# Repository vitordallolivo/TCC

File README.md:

<div align="center">

# DESENVOLVIMENTO DE SISTEMA DE AQUISIÇÃO COM ESTIMAÇÃO POR MODO DESLIZANTE PARA BANCADA DE PROPULSÃO COM MOTOR BLDC

**Trabalho de Conclusão de Curso · Engenharia Elétrica · UDESC Joinville (2026)**

-283272)

</div>

---

## Sumário

- [Sobre o projeto](#sobre-o-projeto)
- [Arquitetura](#arquitetura)
- [Estrutura do repositório](#estrutura-do-repositório)
- [Primeiros passos](#primeiros-passos)
- [Hardware caracterizado](#hardware-caracterizado)
- [Status](#status)
- [Ferramentas](#ferramentas)
- [Declaração de uso de IA](#declaração-de-uso-de-ia)

---

## Sobre o projeto

Este repositório reúne o TCC completo, do firmware ao texto: um **sistema de
aquisição para ensaios de conjuntos motopropulsores com motor BLDC**. Uma placa
de medição lê as tensões e correntes de fase do motor, aciona o ESC e os relés
de potência e envia a telemetria por Ethernet a uma aplicação no PC.

A velocidade e o torque no eixo são **estimados sem sensores mecânicos**, por
um **Observador por Modos Deslizantes (SMO)** com **PLL** executado na própria
placa.

---

## Arquitetura

Uma **placa de medição** (CH32V307, RISC-V 144 MHz, Zephyr RTOS) e uma
**aplicação de supervisão** no PC, ligadas por UDP. Os comandos da placa também
funcionam de qualquer shell, pelo `gui/placa.py`.

```mermaid
flowchart LR
    subgraph PC["gui — supervisão (PySide6)"]
        GUI["GUI + TinyTerminal<br/>placa.py (CLI)"]
        YAML["Config/protocolo.yaml<br/>fonte única do protocolo"]
    end

    PLACA["firmware — placa de medição<br/>fases (V/I) + SMO + PLL, ESC, relés"]
    ESC["ESC"] --> MOTOR["Motor BLDC + hélice"]

    GUI <-->|"UDP 5000 / 5555"| PLACA
    YAML -.->|"generate.py → headers C"| PLACA
    PLACA -->|PWM| ESC
    PLACA -.->|"mede fases"| ESC
```

- **Firmware:** medições e comandos passam por uma fila de trabalho única; a
  aquisição das fases tem fila própria, que roda o observador a cada quadro do
  ADC.
- **Protocolo:** definido só no `gui/Config/protocolo.yaml`. Os headers C do
  firmware são gerados a partir dele, e a GUI lê o mesmo arquivo.
- **Sem a placa:** o firmware também roda como processo Linux (`native_sim`),
  com UDP real em loopback.

Os detalhes estão nos READMEs de cada pasta.

---

## Estrutura do repositório

```text
.
├── firmware/                 Firmware Zephyr da placa de medição
├── gui/                      Aplicação de supervisão, CLI, protocolo e scripts
│   ├── Config/               protocolo.yaml, templates Jinja2 e generate.py
│   ├── Scripts/              Simulação do SMO, autotuning, coeficientes da hélice
│   └── Ensaios/              Scripts e registros dos ensaios
├── docs/
│   ├── TCC_documento/        Texto do TCC em LaTeX (abnTeX2, modelo UDESC)
│   └── TCC_apresentacao/     Slides da defesa em Beamer
├── legado/                   Código antigo fora do build
├── Simulacoes/               LTspice e FEMM (sensor de corrente)
├── Esquematicos/             Esquemáticos
└── Figuras/                  Figuras usadas fora do LaTeX
```

| Pasta | Documentação |
|---|---|
| `firmware/` | [Firmware da placa de medição](firmware/README.md) |
| `gui/` | [Aplicação de supervisão](gui/README.md) · [Geração do protocolo](gui/Config/README.md) |
| `docs/TCC_documento/` | [Como compilar o texto](docs/TCC_documento/README.md) |
| `docs/TCC_apresentacao/` | [Como compilar os slides](docs/TCC_apresentacao/README.md) |

---

## Primeiros passos

Atalhos do `Makefile` da raiz (`make help`):

```bash
make gui            # aplicação de supervisão
make protocolo      # regenera os headers C a partir do protocolo.yaml
make firmware       # compila para a placa (requer Zephyr SDK e west)
make flash          # grava na placa
make native_sim     # compila o firmware para rodar no PC (Linux)
make documento      # texto do TCC
make apresentacao   # slides
```

Comandos da placa pela linha de comando:

```bash
cd gui
.venv/bin/python placa.py tele                    # telemetria
.venv/bin/python placa.py set i_a linear 0.0809   # calibração
```

---

## Hardware caracterizado

| Item | Especificação |
|---|---|
| Motor | Scorpion A-5025-310Kv |
| Bateria | LiPo 6S 3300 mAh 40C |
| Hélices | APC 15×6E e APC 17×10E |
| MCU | WCH CH32V307VCT6, RISC-V 144 MHz, ADC 12 bits, Ethernet integrada |

**Parâmetros elétricos medidos (por fase, estrela)**

| Parâmetro | Valor | Método |
|---|---|---|
| Resistência | R_Y = 8,69 mΩ | 4 fios (Kelvin), R_Y = R_LL/2 |
| Indutância | L_Y ≈ 11,3 µH | Registros de osciloscópio (análise harmônica do circuito de fase) |

---

## Status

| Componente | Estado |
|---|---|
| Firmware | Fases (V/I), SMO + PLL, ESC, relés e segurança; compila para a placa e para `native_sim` |
| Aplicação de supervisão e CLI | Funcionais com a placa, com o simulador e com o `native_sim` |
| Simulação do SMO e autotuning | Validados |
| Parâmetros elétricos do motor | Medidos |
| Ensaios com as hélices APC 15x6E e 17x10E | Concluídos |

---

## Ferramentas

| Área | Ferramentas |
|---|---|
| Hardware | KiCad, LTspice, FEMM |
| Firmware | Zephyr RTOS, Zephyr SDK, OpenOCD (WCH-LinkE) |
| Software | Python, PySide6, pyqtgraph, NumPy, SciPy, Numba, Jinja2 |
| Texto | LaTeX (abnTeX2), TikZ, Beamer |

---

## Declaração de uso de IA

Ferramentas de IA generativa (ChatGPT, Claude, Gemini, DeepSeek, Claude Code)
foram usadas como apoio à revisão textual, à conferência de cálculos e ao
desenvolvimento e depuração de scripts. Todo o conteúdo foi revisado e validado
pelo autor, que assume responsabilidade integral pela precisão e originalidade.

Distribuído sob a licença [MIT](LICENSE).

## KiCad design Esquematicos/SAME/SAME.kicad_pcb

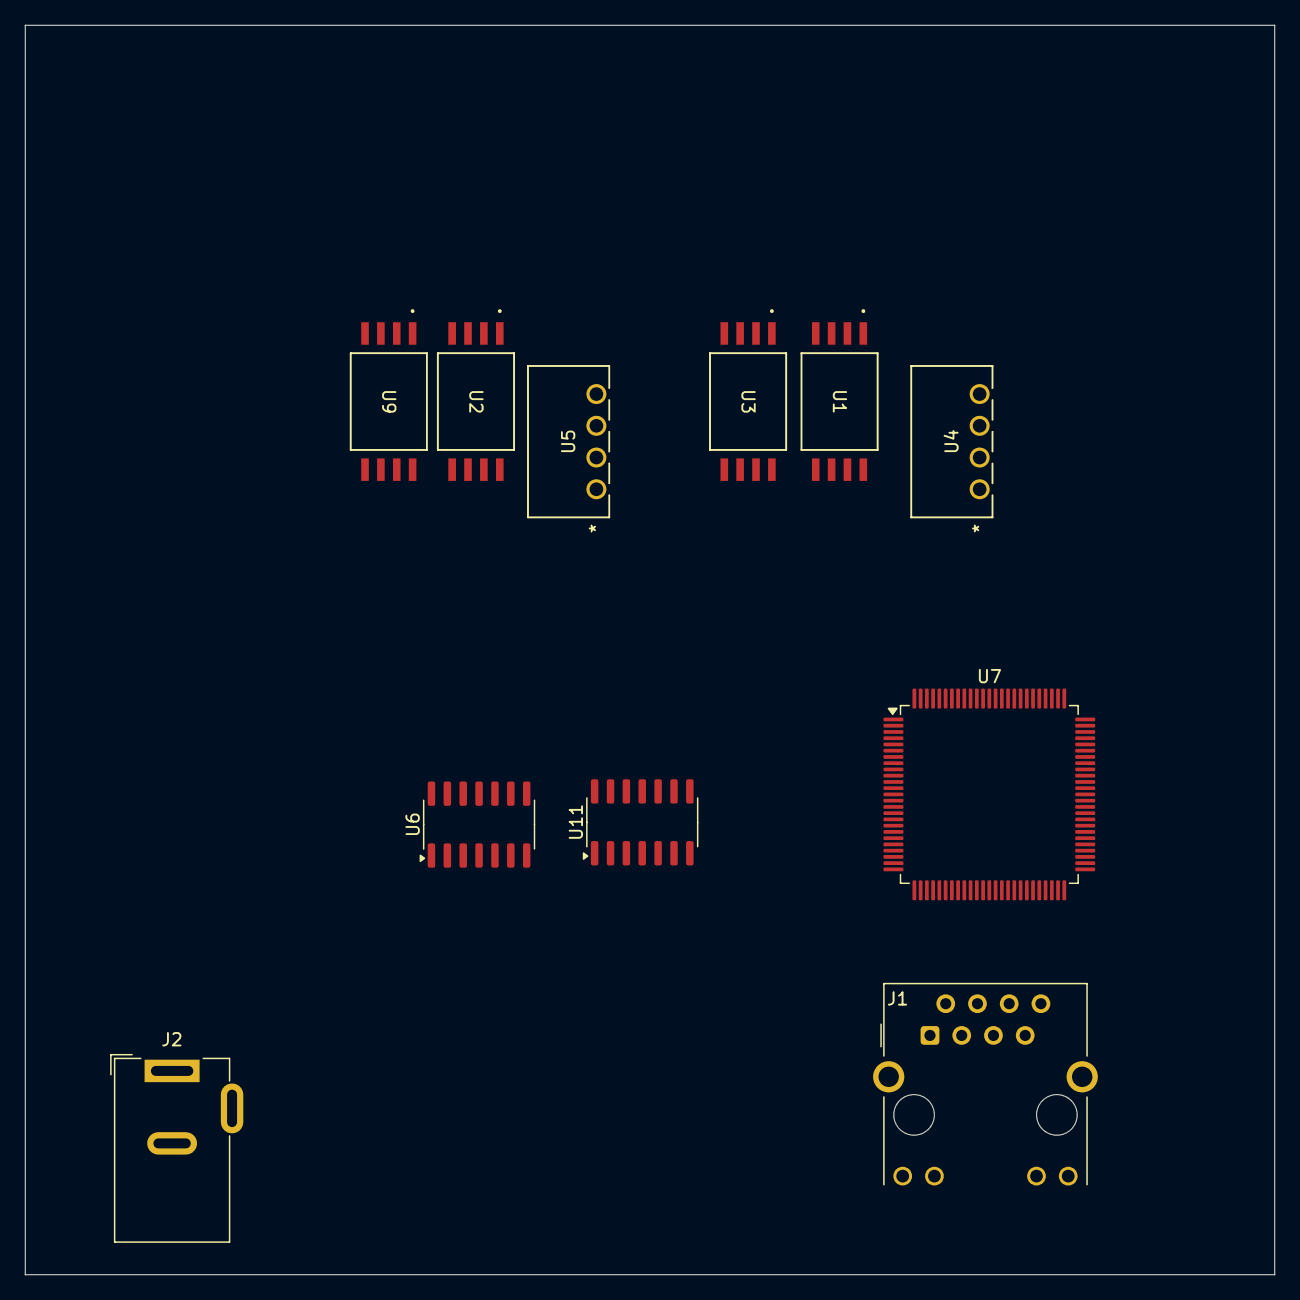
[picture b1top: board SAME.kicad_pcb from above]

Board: 2 copper layers, 100.0 x 100.0 mm, 11 parts (0 on the bottom side), 14 nets, no tracks yet.

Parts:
J1: RJ45_Hanrun_HR911105A_Horizontal
J2: Barrel_Jack_MountingPin; BarrelJack_Wuerth_6941xx301002
U1, U2, U3, U9: AMC1301QDWVRQ1; DWV_8_TEX
U4, U5: B0505S-1WR2; B0505S-1WR2_MNS
U6, U11: MCP6004; SOIC-14_3.9x8.7mm_P1.27mm
U7: CH32V30xVxTx; LQFP-100_14x14mm_P0.5mm

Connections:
+3.3V: J1.4 (TCT), J1.5 (RCT), U1.8 (VDD2), U2.8 (VDD2), U3.8 (VDD2), U6.4 (V+), U9.8 (VDD2), U11.4 (V+)
+5V: U4.2 (VIN), U5.2 (VIN)
/5V1: U1.1 (VDD1), U3.1 (VDD1), U4.4 (+VO)
/5V2: U2.1 (VDD1), U5.4 (+VO), U9.1 (VDD1)
GND: J1.8, J1.SH, J2.2, U1.5 (GND2), U2.5 (GND2), U3.5 (GND2), U4.1 (GND), U5.1 (GND), U6.11 (V-), U9.5 (GND2), U11.11 (V-)
GND2: U1.4 (GND1), U3.4 (GND1), U4.3 (0V)
GND3: U2.4 (GND1), U5.3 (0V), U9.4 (GND1)
unnamed: U6.1, U6.2 (-)
unnamed: U6.6 (-), U6.7
unnamed: U6.8, U6.9 (-)
unnamed: U6.13 (-), U6.14
unnamed: U7.11 (VDD), U7.28 (VDD), U7.75 (VDD)
unnamed: U7.50 (VIO), U7.100 (VIO)
unnamed: U7.10 (VSS), U7.27 (VSS), U7.49 (VSS), U7.74 (VSS), U7.99 (VSS)

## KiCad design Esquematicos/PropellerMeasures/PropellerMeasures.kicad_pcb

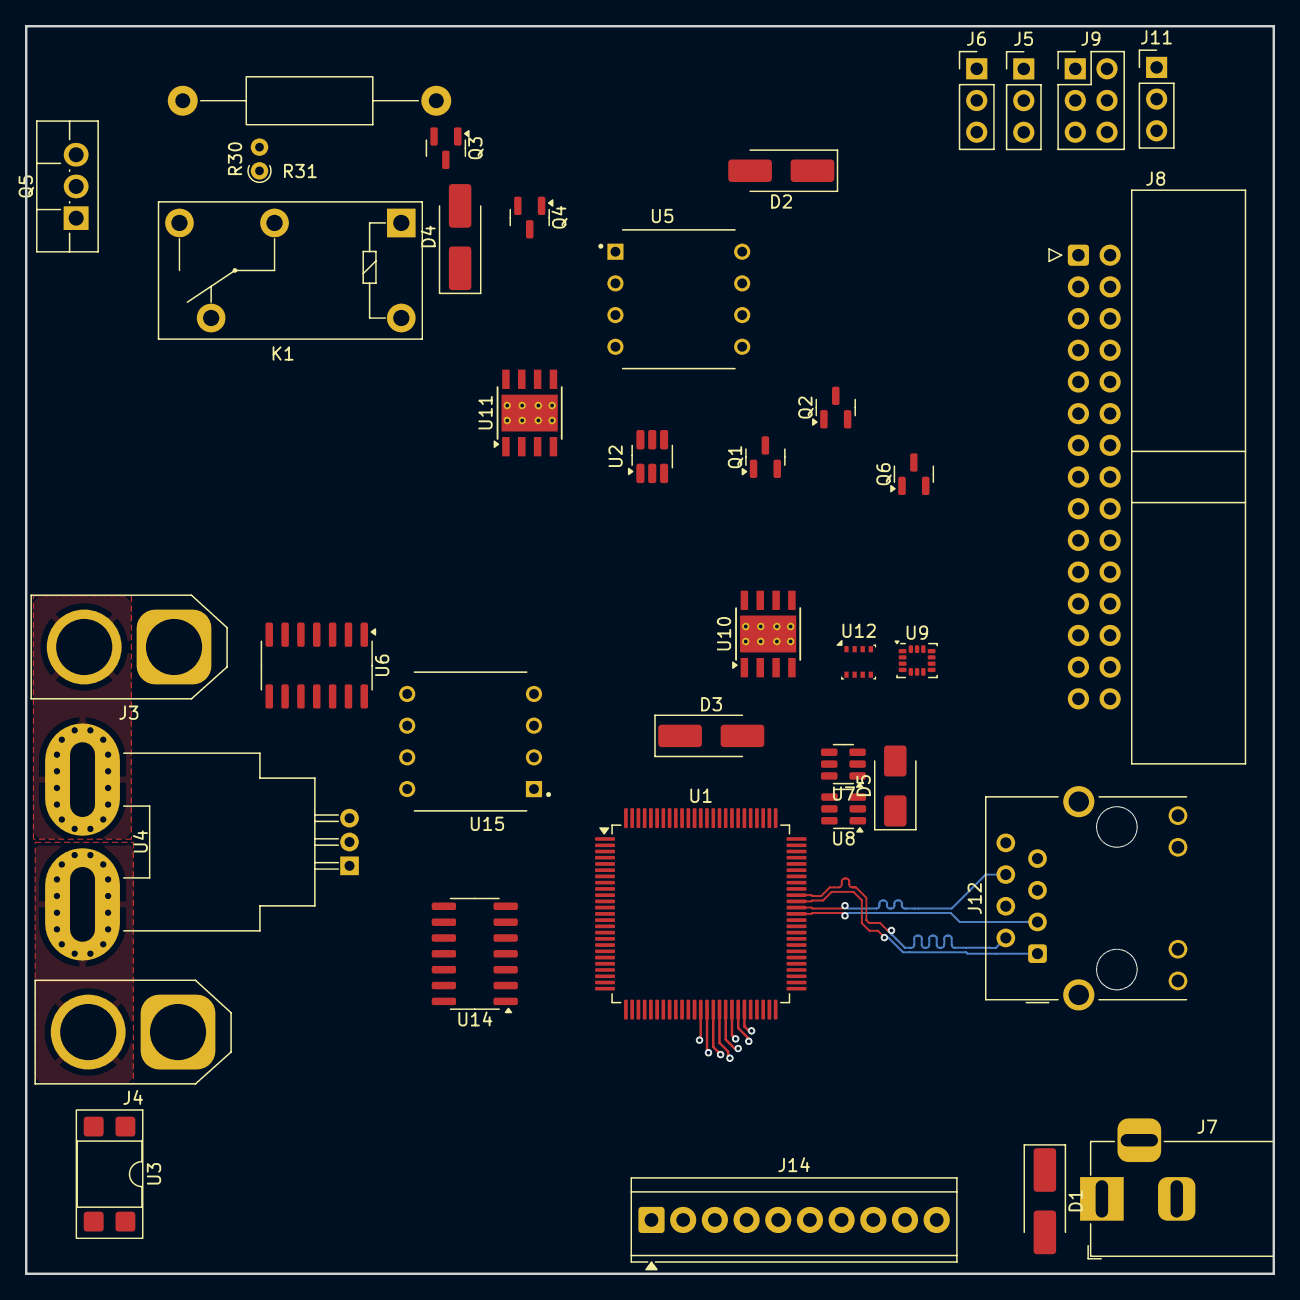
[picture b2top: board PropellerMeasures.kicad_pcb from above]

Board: 4 copper layers, 100.0 x 100.0 mm, 38 parts (0 on the bottom side), 61 nets.

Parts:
D1, D2, D3, D4: M1 THRU M7; D_SMA_Handsoldering
D5: SMAJ5.0CA; D_SMA
J3: Conn_01x02; AMASS_XT60-F_1x02_P7.20mm_Vertical
J4: Conn_01x02; AMASS_XT60-M_1x02_P7.20mm_Vertical
J5: Infravermelho; PinHeader_1x03_P2.54mm_Vertical
J6: TuboPitot; PinHeader_1x03_P2.54mm_Vertical
J7: EXT_PSU; BarrelJack_Horizontal
J8: 2.54-2*15P弯简牛; IDC-Header_2x15_P2.54mm_Horizontal
J9: SWD Header; PinHeader_2x03_P2.54mm_Vertical
J11: PWM ESC; PinHeader_1x03_P2.54mm_Vertical
J12: RJ45_Hanrun_HR911105A_Horizontal
J14: Rele Terminal; TerminalBlock_TE_1-282834-0_1x10_P2.54mm_Horizontal
K1: G5Q-14 DC5; Relay_SPDT_Omron-G5Q-1
Q1, Q2, Q4: BC847; SOT-23
Q3, Q6: MMBT3906; SOT-23
Q5: 2sc4793; TO-220F-3_Vertical
R30: 220; R_Axial_DIN0204_L3.6mm_D1.6mm_P1.90mm_Vertical
R31: 5ohm+-10% 2W (minimo); R_Axial_DIN0411_L9.9mm_D3.6mm_P20.32mm_Horizontal
U1: CH32V307VCT6; LQFP-100_14x14mm_P0.5mm
U2: 74LVC1G11; SOT-23-6_Handsoldering
U3: PC817; DIP-4_W7.62mm_SMDSocket_SmallPads
U4: ACS758xCB-100U-PFF; Allegro_CB_PFF
U5, U15: HCNR201; DIP1016W48P254L1112H510Q8
U6, U14: MCP6004; SOIC-14_3.9x8.7mm_P1.27mm
U7, U8: TPS79301-EP; SOT-23-6
U9: LSM6DSL; LGA-14_3x2.5mm_P0.5mm_LayoutBorder3x4y
U10, U11: TPS54336ADDA; TI_SO-PowerPAD-8_ThermalVias
U12: Bosch_LGA-8_2.5x2.5mm_P0.65mm_ClockwisePinNumbering

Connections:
+3.3V: J5.1, J6.2, J8.1, J8.5, J8.9, J8.13, J8.19, J8.25, J8.29, J12.4 (TCT), J12.5 (RCT), U1.22 (VDDA), U4.1 (VCC), U7.6 (OUT), U9.5 (VDDIO), U9.8 (VDD), U12.6 (VDDIO), U12.8 (VDD), U14.4 (V+)
+5V: D3.1 (K), D4.1 (K), D5.2 (A2), K1.5, U2.5 (VCC), U7.1 (IN), U7.3 (EN), U8.1 (IN), U8.3 (EN)
/BatterySide/ADC_Batt_Vout: U1.23 (PA0), U14.1
/BatterySide/ADC_Iout: U1.24 (PA1), U14.6 (-), U14.7
/BatterySide/Discharger_Battery: K1.3, Q5.1 (C)
/BatterySide/MCU_SignalReady: U1.46 (PE15), U2.3
/BatterySide/OptoSig: Q2.3 (C), U2.6
/BatterySide/Vbatt: J3.2, K1.2, U4.4 (IP+), U11.2 (VIN)
/BatterySide/VrefCurrentMirror: U1.29 (PA4), U14.10 (+)
/MicrocontrollerSch/ACT: J12.11, U1.16 (PC1)
/MicrocontrollerSch/Analog_Pitot: J6.3, U1.25 (PA2)
/MicrocontrollerSch/DT_1: J8.3, U1.45 (PE14)
/MicrocontrollerSch/DT_2: J8.6, U1.43 (PE12)
/MicrocontrollerSch/DT_3: J8.10, U1.41 (PE10)
/MicrocontrollerSch/DT_4: J8.14, U1.39 (PE8)
/MicrocontrollerSch/DT_5: J8.27, U1.5 (PE6)
/MicrocontrollerSch/DT_6: J8.23, U1.3 (PE4)
/MicrocontrollerSch/I2C1_Remap_SCL: J8.16, U1.95 (PB8), U9.13 (SCL), U12.4 (SCK)
/MicrocontrollerSch/I2C1_Remap_SDA: J8.17, U1.96 (PB9), U9.14 (SDA), U12.3 (SDA)
/MicrocontrollerSch/LINK: J12.10, U1.15 (PC0)
/MicrocontrollerSch/PWM_ESC: J11.2, U1.92 (PB6)
/MicrocontrollerSch/RXN: J12.6 (RD-), U1.64 (PC7)
/MicrocontrollerSch/RXP: J12.3 (RD+), U1.63 (PC6)
/MicrocontrollerSch/RX_USART: J9.1, U1.69 (PA10)
/MicrocontrollerSch/Rele_Ensaio_Corrente_Fan_1: J14.8, U1.53 (PB14)
/MicrocontrollerSch/Rele_Ensaio_Corrente_Fan_2: J14.6, U1.52 (PB13)
/MicrocontrollerSch/Rele_Ensaio_Corrente_Pastilha_1: J14.4, U1.51 (PB12)
/MicrocontrollerSch/Rele_Ensaio_Corrente_Pastilha_2: J14.2, U1.48 (PB11)
/MicrocontrollerSch/SCK_1: J8.2, U1.44 (PE13)
/MicrocontrollerSch/SCK_2: J8.7, U1.42 (PE11)
/MicrocontrollerSch/SCK_3: J8.11, U1.40 (PE9)
/MicrocontrollerSch/SCK_4: J8.15, U1.38 (PE7)
/MicrocontrollerSch/SCK_5: J8.28, U1.4 (PE5)
/MicrocontrollerSch/SCK_6: J8.24, U1.2 (PE3)
/MicrocontrollerSch/SWCLK: J9.4, U1.76 (SWCLK)
/MicrocontrollerSch/SWDIO: J9.2, U1.72 (SWDIO)
/MicrocontrollerSch/TXN: J12.2 (TD-), U1.66 (PC9)
/MicrocontrollerSch/TXP: J12.1 (TD+), U1.65 (PC8)
/MicrocontrollerSch/TX_USART: J9.3, U1.68 (PA9)
/MicrocontrollerSch/VDDA: U1.11 (VDD), U1.21 (VREF+), U1.28 (VDD), U1.50 (VIO), U1.75 (VDD), U1.100 (VIO), U8.6 (OUT)
/PowerSupply/8V ~ 24 V (DC): D1.2 (A), J7.1
GND: D5.1 (A1), J5.2, J6.1, J7.2, J8.4, J8.8, J8.12, J8.18, J8.22, J8.26, J8.30, J9.5, J11.3, J12.8, J12.SH, J14.1, J14.3, J14.5, J14.7, J14.9, J14.10, Q1.2 (E), Q2.2 (E), Q4.2 (E), Q6.3 (C), U1.10 (VSS), U1.19 (VSSA), U1.20 (VREF-), U1.27 (VSS), U1.49 (VSS), U1.74 (VSS), U1.99 (VSS), U2.2 (GND), U3.3, U4.2 (GND), U5.5, U7.2 (GND), U8.2 (GND), U9.6 (GND), U9.7 (GND), U10.4 (GND), U10.9 (ETPAD), U12.1 (GND), U12.7 (GND), U14.3 (+), U14.11 (V-), U14.12 (+), U15.4
GND2: J3.1, J4.1, Q3.3 (C), R31.2, U3.2, U5.4, U6.5 (+), U6.10 (+), U6.11 (V-), U11.4 (GND), U11.9 (ETPAD), U15.5
unnamed: D3.2 (A), J9.6
unnamed: D4.2 (A), K1.1, Q4.3 (C)
unnamed: J4.2, U4.5 (IP-)
unnamed: Q3.1 (B), U6.7
unnamed: Q3.2 (E), U5.1
unnamed: Q5.2 (B), R30.2
unnamed: Q5.3 (E), R31.1, U6.13 (-)
unnamed: Q6.1 (B), U14.14
unnamed: Q6.2 (E), U15.1
unnamed: R30.1, U6.14
unnamed: U6.1, U6.2 (-)
unnamed: U5.3, U6.6 (-)
unnamed: U6.9 (-), U15.6
unnamed: U6.8, U6.12 (+)
unnamed: U5.6, U14.2 (-)
unnamed: U14.8, U14.9 (-)
unnamed: U14.13 (-), U15.3
VCC: D1.1 (K), D2.1 (K), U10.2 (VIN)

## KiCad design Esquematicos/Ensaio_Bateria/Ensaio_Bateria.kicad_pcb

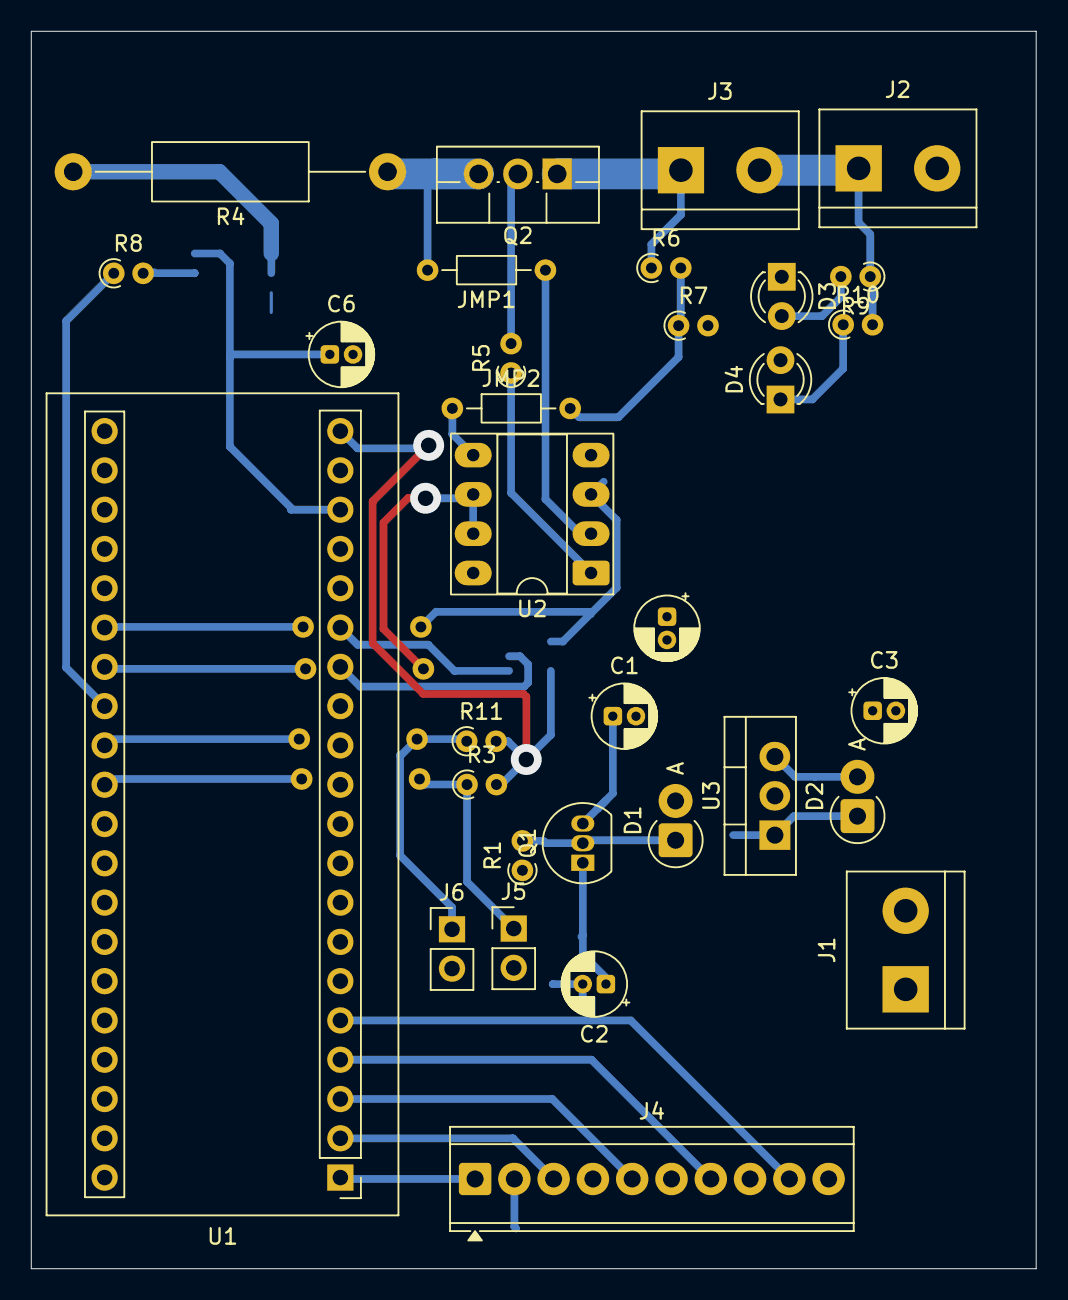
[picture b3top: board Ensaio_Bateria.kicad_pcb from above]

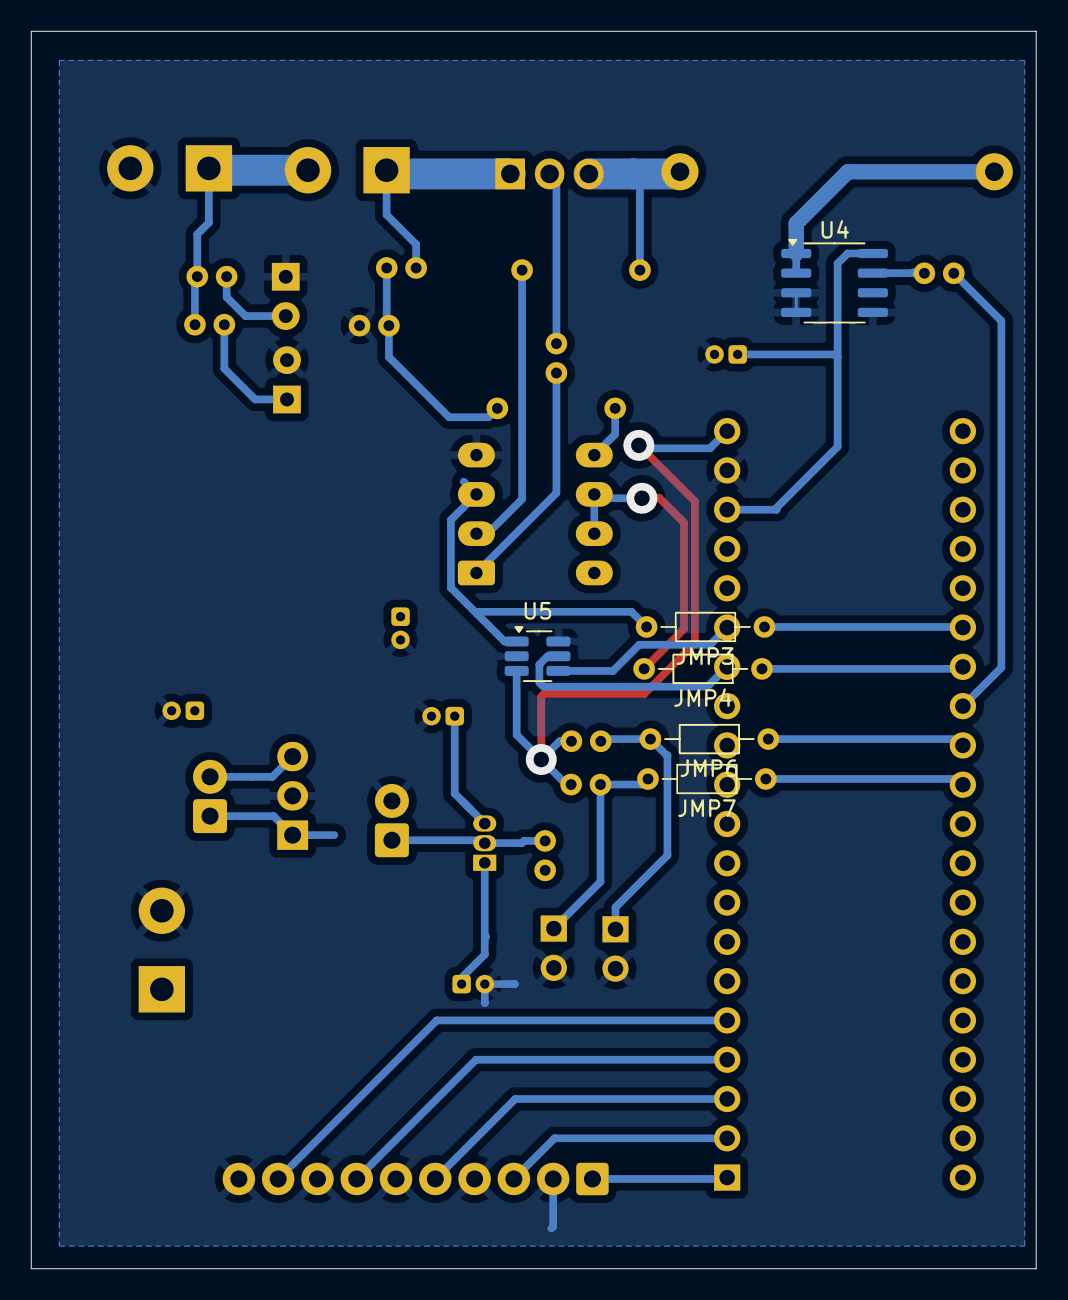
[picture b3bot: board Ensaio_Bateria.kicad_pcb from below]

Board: 2 copper layers, 65.0 x 80.0 mm, 38 parts (6 on the bottom side), 34 nets.

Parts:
C1, C2: 0.1uf; CP_Radial_D4.0mm_P1.50mm
C3, C4, C6: 33n; CP_Radial_D4.0mm_P1.50mm
D1: 8.2; D_DO-41_SOD81_P2.54mm_Vertical_AnodeUp
D2: D; D_DO-41_SOD81_P2.54mm_Vertical_AnodeUp
D3: Verde; LED_D3.0mm
D4: Vermelho; LED_D3.0mm
J1: PWR_Connector; TerminalBlock_bornier-2_P5.08mm
J2: BAT_Connector; TerminalBlock_bornier-2_P5.08mm
J3: rele_BAT_Connector; TerminalBlock_bornier-2_P5.08mm
J4: Reles Conector; TerminalBlock_TE_1-282834-0_1x10_P2.54mm_Horizontal
J5: Termistor_pin_2; PinHeader_1x02_P2.54mm_Vertical
J6: Termistor_pin_1; PinHeader_1x02_P2.54mm_Vertical
JMP1, JMP2, JMP3, JMP4, JMP6, JMP7: 0; R_Axial_DIN0204_L3.6mm_D1.6mm_P7.62mm_Horizontal
Q1: BC547; TO-92_Inline
Q2: 2sc4793; TO-220F-3_Vertical
R1: 2.7k+-10% 0.25W; R_Axial_DIN0204_L3.6mm_D1.6mm_P1.90mm_Vertical
R3, R11: 5k; R_Axial_DIN0204_L3.6mm_D1.6mm_P1.90mm_Vertical
R4: 5ohm+-10% 2W (minimo); R_Axial_DIN0411_L9.9mm_D3.6mm_P20.32mm_Horizontal
R5: 220; R_Axial_DIN0204_L3.6mm_D1.6mm_P1.90mm_Vertical
R6: 27k; R_Axial_DIN0204_L3.6mm_D1.6mm_P1.90mm_Vertical
R7: 3k; R_Axial_DIN0204_L3.6mm_D1.6mm_P1.90mm_Vertical
R8: 2k; R_Axial_DIN0204_L3.6mm_D1.6mm_P1.90mm_Vertical
R9, R10: 2k +-10% 0.5W; R_Axial_DIN0204_L3.6mm_D1.6mm_P1.90mm_Vertical
U1: YAAJ_WeAct_BlackPill_Part_Like; YAAJ_WeAct_BlackPill_2
U2: LM358; DIP-8_W7.62mm_Socket_LongPads
U3: L7805; TO-220-3_Vertical
U4: ACS712xLCTR-05B; SOIC-8_3.9x4.9mm_P1.27mm
U5: MCP4725xxx-xCH; SOT-23-6_Handsoldering

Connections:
+3V3: R3.2, R11.2, U1.20 (3V3), U5.3 (VDD)
+5V: C3.1, C4.1, C6.1, D2.2 (A), U1.18 (5V), U2.8 (V+), U3.3 (OUT), U4.8 (VCC)
+8V: C1.1, D2.1 (K), Q1.3 (E), U3.1 (IN)
+12V: C2.1, J1.1, Q1.1 (C), R1.1
/SCL1: U1.14 (PB6), U5.5 (SCL)
/SDA1: U1.15 (PB7), U5.4 (SDA)
/V_termistor_1: J6.1, JMP6.2, R11.1
/V_termistor_2: J5.1, JMP7.2, R3.1
/Vbat+: J3.1, Q2.1 (C), R6.1
/Vbat_adc: JMP4.2, U2.6 (-), U2.7
/Viout_adc: R8.1, U1.28 (PA2)
/Vopamp_ref: JMP3.2, U2.3 (+), U5.1 (VOUT)
/rele_bateria: J4.9, U1.5 (PA8)
/rele_fan_1: J4.1, U1.1 (PB12)
/rele_fan_2: J4.3, U1.2 (PB13)
/rele_pastilha_fria: J4.5, U1.3 (PB14)
/rele_pastilha_quente: J4.7, U1.4 (PB15)
GND: C1.2, C2.2, C3.2, C4.2, C6.2, D1.2 (A), D3.1 (K), D4.2 (A), J1.2, J2.2, J4.2, J4.4, J4.6, J4.8, J4.10, J5.2, J6.2, R7.2, U1.19 (GND), U2.4 (V-), U3.2 (GND), U4.3 (IP-), U4.4 (IP-), U4.5 (GND), U5.2 (VSS), U5.6 (A0)
unnamed: D1.1 (K), Q1.2 (B), R1.2
unnamed: D3.2 (A), R9.2
unnamed: D4.1 (K), R10.1
unnamed: J2.1, J3.2, R9.1, R10.2
unnamed: JMP2.2, R6.2, R7.1
unnamed: Q2.2 (B), R5.2
unnamed: JMP1.2, Q2.3 (E), R4.1
unnamed: R4.2, U4.1 (IP+), U4.2 (IP+)
unnamed: R5.1, U2.1
unnamed: JMP3.1, U1.26 (PA0)
unnamed: JMP4.1, U1.27 (PA1)
unnamed: JMP6.1, U1.29 (PA3)
unnamed: JMP7.1, U1.30 (PA4)
unnamed: JMP1.1, U2.2 (-)
unnamed: JMP2.1, U2.5 (+)
unnamed: R8.2, U4.7 (VIOUT)

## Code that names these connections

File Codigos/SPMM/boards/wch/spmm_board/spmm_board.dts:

/dts-v1/;
#include <wch/ch32v307/ch32v307vc.dtsi>
#include <zephyr/dt-bindings/gpio/gpio.h>
#include <zephyr/dt-bindings/pinctrl/ch32v20x_30x-pinctrl.h>
#include <zephyr/dt-bindings/pwm/pwm.h>
#include <zephyr/dt-bindings/clock/ch32v20x_30x-clocks.h>

#define CH32V20X_V30X_PINMUX_ADC1_RM 0

/ {
    model = "SPMM Board";
    compatible = "wch,ch32v307";

    chosen {
        zephyr,sram    = &sram0;
        zephyr,flash   = &flash0;
        zephyr,console = &usart1;   /* LOG local para debug de bancada */
    };

    /* ==================================================================
     * MEDICAO COMPLETA — 3 correntes + 3 tensoes de fase (dq real)
     *
     * ADC1 (DMA1 canal 1): correntes de fase
     *   idx 0 -> CH0 / PA0 : Ia
     *   idx 1 -> CH1 / PA1 : Ib
     *   idx 2 -> CH2 / PA2 : Ic
     * ADC2 (DMA1 canal 2): tensoes de fase (para estimar theta_e -> Park)
     *   idx 0 -> CH3 / PA3 : Va
     *   idx 1 -> CH4 / PA4 : Vb
     *   idx 2 -> CH5 / PA5 : Vc
     *
     * Driver custom adc_ch32v307 (NAO o padrao, que conflita com a Ethernet).
     * O driver suporta 2 instancias (ADC1 base 0x40012400, ADC2 base
     * 0x40012800), cada uma com seu proprio canal DMA1.
     *
     * >>> RISCO DE HARDWARE (validar na bancada) <<<
     * Em silicio estilo F103, o ADC2 normalmente NAO possui request de DMA
     * proprio (so ADC1). Se o ADC2 do CH32V307 nao disparar DMA1-ch2, o
     * scan de tensao nao avanca e sera preciso: (a) migrar as tensoes para
     * o ADC1 (6 canais num scan so), ou (b) usar dual-mode simultaneo. Ver
     * CLAUDE.md. As correntes (ADC1) funcionam independentemente disso.
     * ================================================================== */
    adc1: adc@40012400 {
        compatible = "wch,adc";
        reg = <0x40012400 0x400>;
        clocks = <&rcc CH32V20X_V30X_CLOCK_ADC1>;
        interrupt-parent = <&pfic>;
        interrupts = <34>;
        dmas = <&dma1 1>;
        dma-names = "rx";
        pinctrl-0 = <&adc1_default>;
        pinctrl-names = "default";
        status = "okay";
        #io-channel-cells = <1>;
    };

    adc2: adc@40012800 {
        compatible = "wch,adc";
        reg = <0x40012800 0x400>;
        clocks = <&rcc CH32V20X_V30X_CLOCK_ADC2>;
        interrupt-parent = <&pfic>;
        interrupts = <34>;          /* ADC1_2 compartilham a IRQ; driver usa a do DMA */
        dmas = <&dma1 2>;
        dma-names = "rx";
        pinctrl-0 = <&adc2_default>;
        pinctrl-names = "default";
        status = "okay";
        #io-channel-cells = <1>;
    };

    /* ==================================================================
     * TIM3 CH3 (PB0) — input capture do sensor de rotacao
     *   14 polos -> 7 pulsos/volta (Hall) ou disco optico
     * ================================================================== */
    tim3: timer@40000400 {
        compatible = "wch,gptm";
        reg = <0x40000400 0x400>;
        clocks = <&rcc CH32V20X_V30X_CLOCK_TIM3>;
        interrupt-parent = <&pfic>;
        interrupts = <45>;
        channels = <4>;
        status = "okay";
        prescaler = <0>;
    };

    rpm_capture_pin: rpm-capture-pin {
        compatible = "spmm,gpio-array";
        gpios = <&gpiob 0 GPIO_ACTIVE_HIGH>;
    };

    /* ==================================================================
     * TIM4 CH1 (PB6) — PWM de SERVO para o throttle do ESC
     *   Periodo 20ms (50Hz), pulso 1000-2000us (padrao RC).
     *   prescaler=143 -> 1 tick = 2us @ 72MHz (base de servo, NAO potencia)
     * ================================================================== */
    tim4: timer@40000800 {
        compatible = "wch,gptm";
        reg = <0x40000800 0x400>;
        clocks = <&rcc CH32V20X_V30X_CLOCK_TIM4>;
        interrupt-parent = <&pfic>;
        interrupts = <46>;
        channels = <4>;
        prescaler = <143>;
        status = "okay";

        pwm4: pwm {
            compatible = "wch,gptm-pwm";
            #pwm-cells = <3>;
            pinctrl-0 = <&tim4_ch1_default>;
            pinctrl-names = "default";
            status = "okay";
        };
    };

    esc_motor: esc-motor {
        compatible = "spmm,pwm-consumer";
        pwms = <&pwm4 1 PWM_USEC(20000) PWM_POLARITY_NORMAL>;
    };
};

/* ==================================================================== *
 * PINCTRL                                                               *
 * ==================================================================== */

&pinctrl {

    adc1_default: adc1_default {
        group1 {
            pinmux = <CH32V20X_V30X_PINMUX_DEFINE(PA, 0, ADC1, 0)>;   /* CH0 - Ia */
        };
        group2 {
            pinmux = <CH32V20X_V30X_PINMUX_DEFINE(PA, 1, ADC1, 0)>;   /* CH1 - Ib */
        };
        group3 {
            pinmux = <CH32V20X_V30X_PINMUX_DEFINE(PA, 2, ADC1, 0)>;   /* CH2 - Ic */
        };
    };

    adc2_default: adc2_default {
        group1 {
            pinmux = <CH32V20X_V30X_PINMUX_DEFINE(PA, 3, ADC1, 0)>;   /* CH3 - Va */
        };
        group2 {
            pinmux = <CH32V20X_V30X_PINMUX_DEFINE(PA, 4, ADC1, 0)>;   /* CH4 - Vb */
        };
        group3 {
            pinmux = <CH32V20X_V30X_PINMUX_DEFINE(PA, 5, ADC1, 0)>;   /* CH5 - Vc */
        };
    };

    usart1_default: usart1_default {
        group1 {
            pinmux = <USART1_TX_PA9_0>;
            output-high;
            drive-push-pull;
            slew-rate = "max-speed-10mhz";
        };
        group2 {
            pinmux = <USART1_RX_PA10_0>;
            bias-pull-up;
        };
    };

    tim4_ch1_default: tim4_ch1_default {
        group1 {
            pinmux = <CH32V20X_V30X_PINMUX_DEFINE(PB, 6, TIM4, 0)>;
            drive-push-pull;
            slew-rate = "max-speed-50mhz";
        };
    };

    mac_default: mac_default {
        mac_internal_rxp {
            pinmux = <CH32V20X_V30X_PINMUX_DEFINE(PC, 6, ETH, 0)>;
            slew-rate = "max-speed-50mhz";
        };
        mac_internal_rxn {
            pinmux = <CH32V20X_V30X_PINMUX_DEFINE(PC, 7, ETH, 0)>;
            slew-rate = "max-speed-50mhz";
        };
        mac_internal_txp {
            pinmux = <CH32V20X_V30X_PINMUX_DEFINE(PC, 8, ETH, 0)>;
            slew-rate = "max-speed-50mhz";
        };
        mac_internal_txn {
            pinmux = <CH32V20X_V30X_PINMUX_DEFINE(PC, 9, ETH, 0)>;
            slew-rate = "max-speed-50mhz";
        };
    };

    mdio_default: mdio_default {
        /* PHY interno - sem pinos MDIO externos necessarios */
    };
};

/* ==================================================================== *
 * CLOCKS / GPIO / PERIFERICOS                                           *
 * ==================================================================== */

&clk_hse { status = "okay"; };
&pll     { clocks = <&clk_hse>; status = "okay"; };
&rcc     { clocks = <&pll>; };

&gpioa { status = "okay"; };
&gpiob { status = "okay"; };
&gpioc { status = "okay"; };

/* dma1 fica "disabled" como CONTROLLER GENERICO Zephyr (dma_wch.c): o driver
 * custom adc_ch32v307.c NAO usa a API generica de DMA (faz MMIO direto), so
 * precisa da celula "channel" de `dmas = <&dma1 1>` (resolvida em compile
 * time). Deixar dma1 "okay" faria dma_wch e adc_ch32v307 disputarem a mesma
 * IRQ do canal 1 = conflito. Ver comentario identico na SIBA. */
&dma1 { status = "disabled"; };

&usart1 {
    status = "okay";
    current-speed = <115200>;
    pinctrl-0 = <&usart1_default>;
    pinctrl-names = "default";
};

/* Ethernet interno (Telnet + log UDP). FIXES herdados da SIBA:
 *  - &eth okay: habilita o controller pai (sobe o clock do MAC).
 *  - local-mac-address fixo: evita leitura da OTP (que, zerada, trava o boot).
 *  - internal-phy-pllmul/prediv: HSE 8MHz / prediv2=2 * pllmul=15 = 60MHz. */
&eth  { status = "okay"; };

&mac {
    status = "okay";
    pinctrl-0 = <&mac_default>;
    pinctrl-names = "default";
    phy-connection-type = "internal";
    phy-handle = <&eth_phy>;
    local-mac-address = [02 00 00 05 02 07];
    internal-phy-pllmul = "15";
    internal-phy-prediv = "2";
};

&mdio {
    status = "okay";
    pinctrl-0 = <&mdio_default>;
    pinctrl-names = "default";
    eth_phy: ethernet-phy@0 {
        compatible = "ethernet-phy";
        reg = <0x00>;
    };
};

&rng { status = "okay"; };

&sram0  { reg = <0x20000000 DT_SIZE_K(128)>; };
&flash0 { reg = <0x08000000 DT_SIZE_K(198)>; };

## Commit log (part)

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2026-02-18 Criando Repositorio dos codigos do TCC
2026-02-18 atualizando gitignore
2026-02-19 Esquematico PropellerSide
2026-02-28 InicioProjetoInversorBLDC
2026-03-12 PSU do propeller e simulação
2026-03-12 Remove o arquivo
2026-03-12 Adiciona .venv ao gitignore
2026-04-08 Programa de usuario mudado
2026-04-11 Exclusão de metodos antigos e oficialização do uso do Zephyr, começando pela SIBA ( Sistema Interligado Bancada e Aerodinamica)
2026-04-12 Adicionando NCI, OSSI e as lib que eu esqueci anteriormente
2026-04-12 Implementado dupla conexão da network e ajustado a consistencia do TCKEC
2026-04-15 Mudança para entry point ser no Vcore
2026-04-22 Simulacoes EKF e SMO
2026-04-25 Melhorias do SMO
2026-04-25 Using .yaml to automation of C files
2026-04-26 Alteração GUI e mais modularidade
2026-04-26 atualização na GUI, funções de persistencia e conexão dos yaml com python
2026-04-26 Criação de uma ferramenta para testes os TinyTerminal e melhorias
2026-04-26 Ajeitando GUI e comando de Restart
2026-04-26 Mensagem de boas vindas
2026-05-02 Atualização Siba design
2026-05-13 Criação da SAME como PCB e modificações SIBA
2026-05-14 Corregindo o arquivo dos requeriments
2026-05-17 melhorando medições da SAME para custo beneficio e melhorias no sistema de graficos
2026-05-20 Topologia para simulação do SMO
    Resumindo agora o SMO usa PLL + uma iteração, para
    encontrar o back-emf que reduz bastante o erro
2026-05-20 Add additional sensor configurations to SAME and SIBA YAML files
2026-05-25 Melhorias no algoritmo de identificação do SMO
    Usa o RMS para calculo do K_SMO, e media para K_real,
    não precisa mais filtrar tbm
2026-06-07 Mudanças dos templates e implementaçÃo das camadas
2026-06-07 feat: Implement Propeller Manager for motor current protection and throttle control
    - Added Propeller_Manager.c and Propeller_Manager.h to manage motor/ESC operations.
    - Introduced functions to set maximum current and request throttle while ensuring current limits are respected.
    - Integrated Propeller_Manager into System_Manager for real-time updates based on battery current.
    - Created Test_Shell.c and Test_Shell.h to expose commands for testing via Zephyr Shell, allowing manual control of the ESC and battery settings.
    - Updated Battery_Manager to support dynamic cell count detection and user-defined settings.
    - Refactored Log_Manager to transmit telemetry data periodically without a dedicat
2026-06-07 Refactor SYS management: consolidate System_Manager into Sys
    - Introduced Sys.c and Sys.h to manage the SYS layer, handling sensor updates and telemetry transmission.
    - Removed System_Manager.h and its associated initialization.
    - Updated Log_Manager to include error_code in telemetry logs.
    - Enhanced Propeller_Manager with load cell calibration and health checks.
    - Integrated Security_Manager for error detection and handling across various sensors.
    - Updated Test_Shell commands to directly interact with the new Sys layer and its managers.
2026-06-10 Implementa suporte para I2C e DAC no HAL, adiciona comandos de shell para I2C e DAC, e ajusta calibração de sensores
    - Adiciona definições e funções para I2C e DAC no HAL.h, incluindo leitura, escrita e calibração.
    - Implementa comandos de shell para varredura, leitura e escrita no barramento I2C, além de controle do DAC.
    - Atualiza a configuração do projeto para habilitar I2C e desabilitar log de depuração do ADC.
    - Refatora a lógica de calibração de sensores no Test_Shell.c para utilizar os novos métodos de calibração.
    - Remove loop de heartbeat no main.c, permitindo que o scheduler do Zephyr assuma o controle.
2026-06-11 Correcting bug with ETH module
2026-06-11 tentando corrigir
2026-06-13 Fazendo driver do ADC e ETH funcionar :D
2026-06-21 Add SMO gains configuration and simulation scripts
    - Introduced `smo_gains.json` for storing SMO gains and configuration parameters.
    - Added `test_coeff_auto.py` for simulating the SMO and performing autotuning.
    - Updated `Readme.md` to include detailed project description, objectives, repository structure, and hardware specifications.
    - Created initial log files for LTspice simulations in `Simulacoes/Medicoes`.
2026-06-21 Add initial documentation for SPMM project
